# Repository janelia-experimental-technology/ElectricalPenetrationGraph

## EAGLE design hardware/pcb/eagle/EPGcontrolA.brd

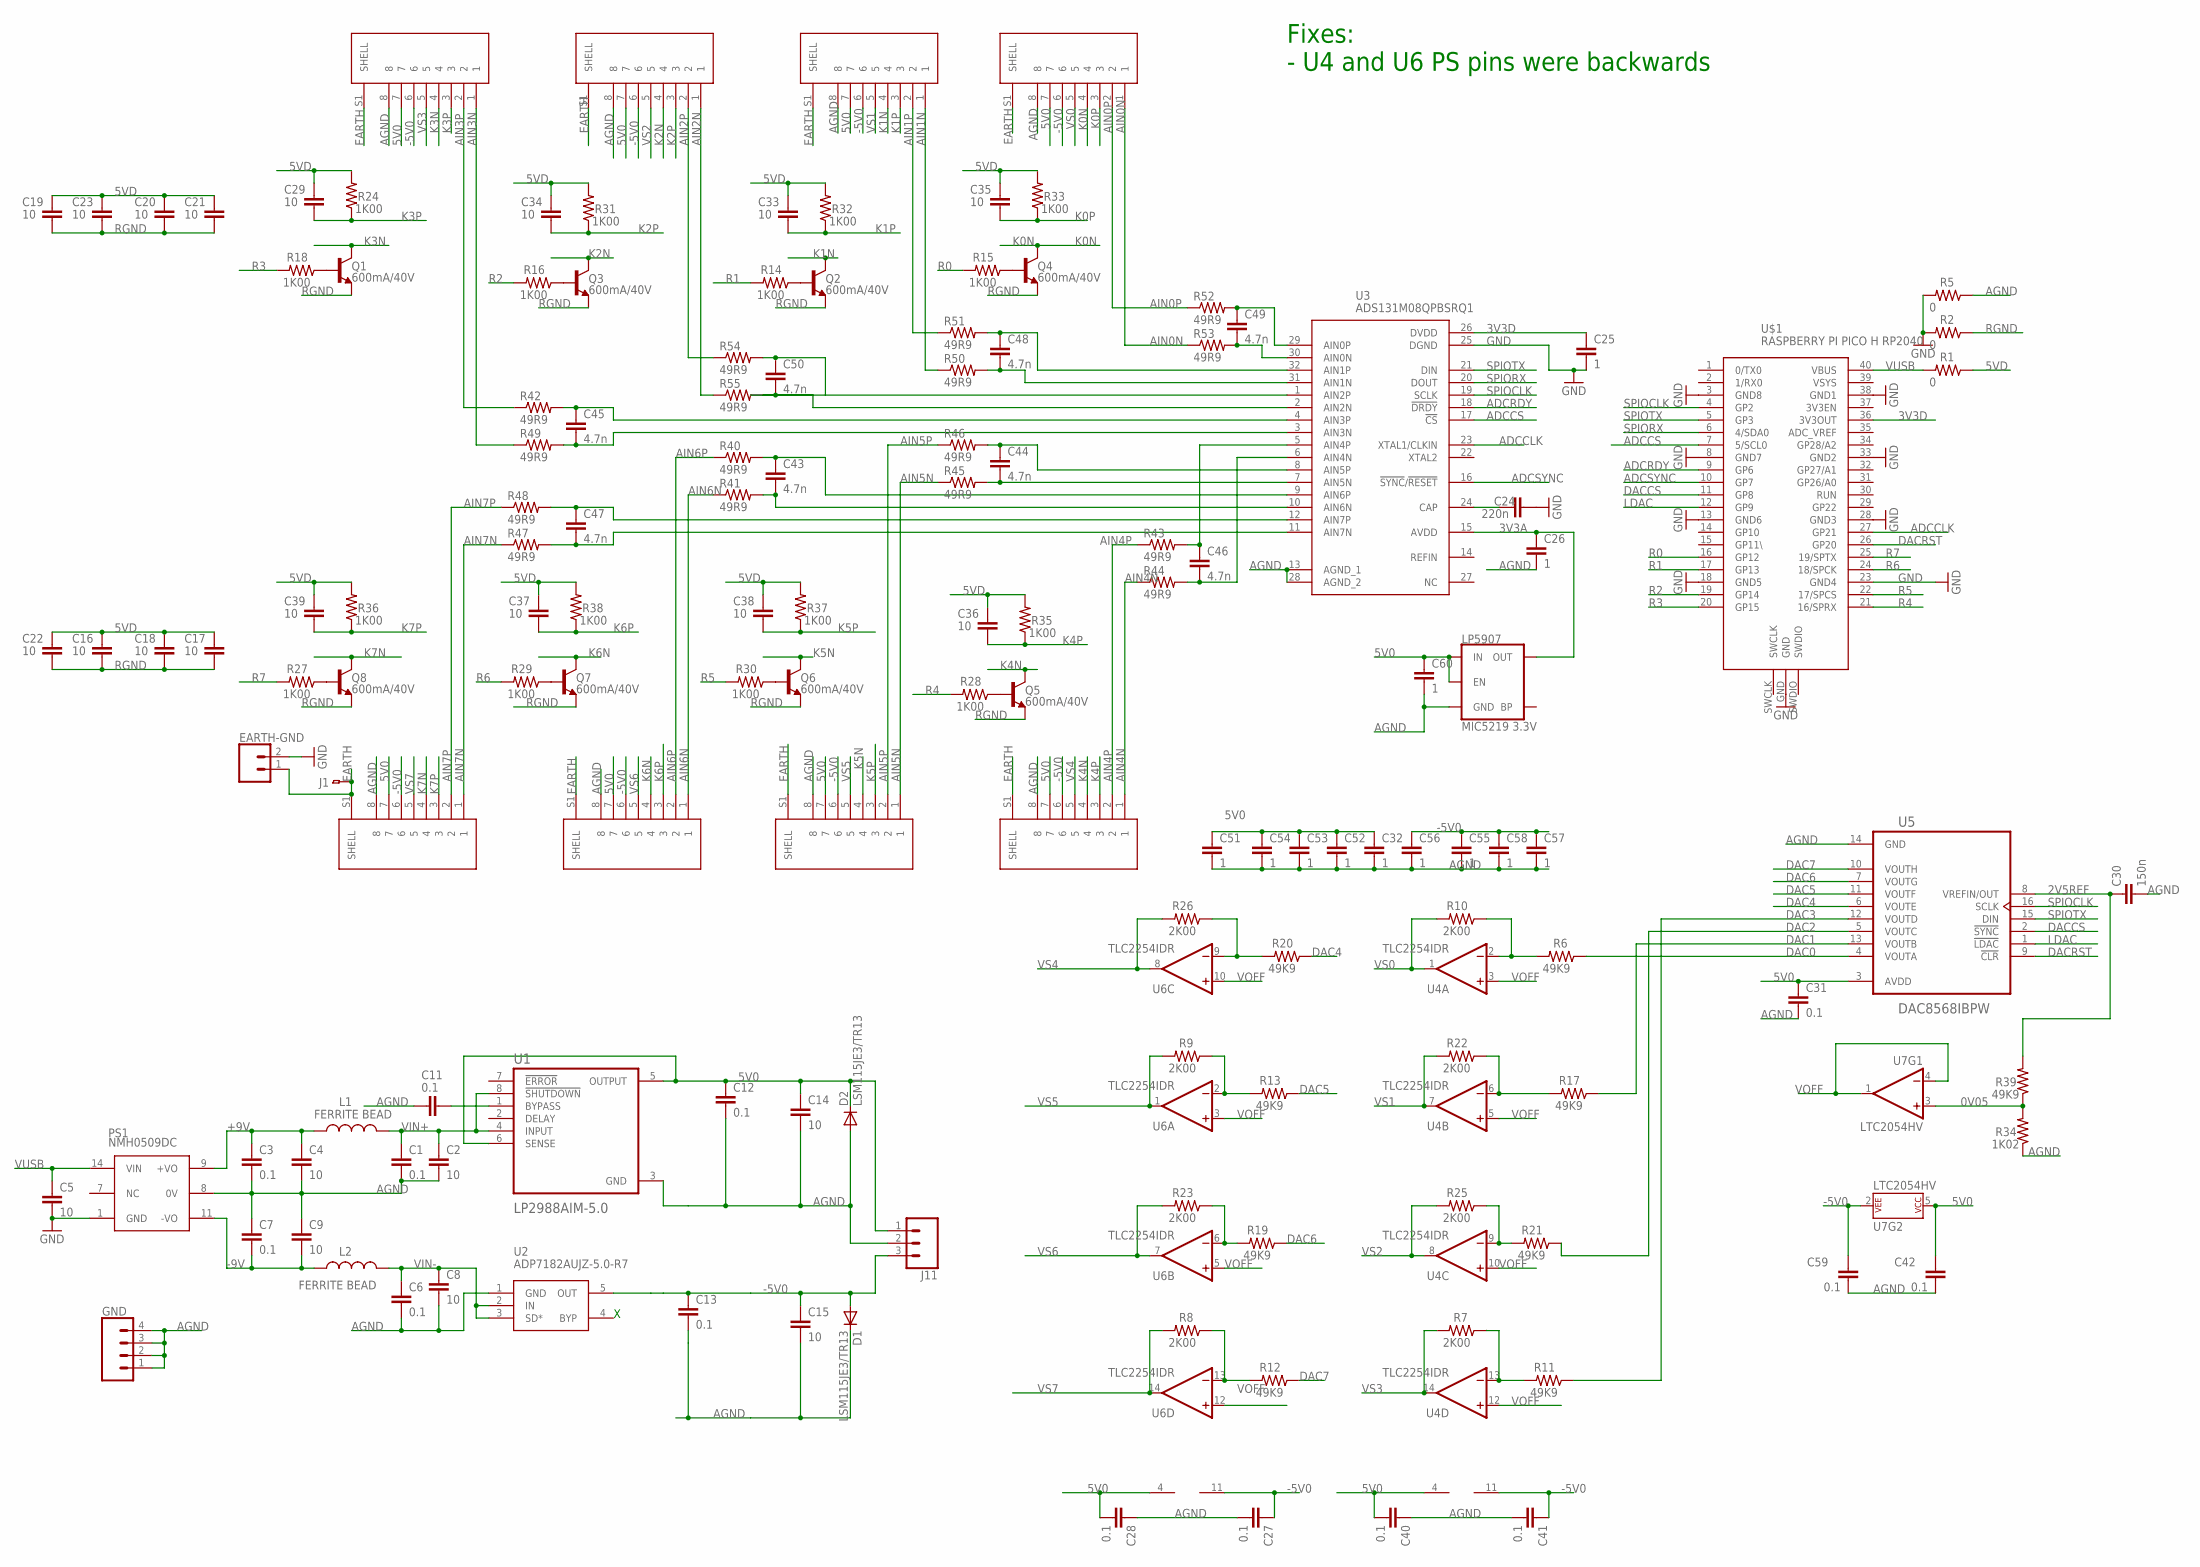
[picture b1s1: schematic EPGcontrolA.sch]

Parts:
C1, C3, C6, C7, C11, C12, C13, C27, C28, C31, C40, C41, C42, C59: 0.1; 0603S
C2, C4, C5, C8, C9, C14, C15: 10; C1206
C16, C17, C18, C19, C20, C21, C22, C23, C29, C33, C34, C35, C36, C37, C38, C39: 10; 1206S
C24: 220n; 0603S
C25, C26, C32, C51, C52, C53, C54, C55, C56, C57, C58, C60: 1; 0805S
C30: 150n; 0603S
C43, C44, C45, C46, C47, C48, C49, C50: 4.7n; 0805S
D1, D2: LSM115JE3/TR13; SMA-DIODE
EARTH-GND: CONN_02LOCK; 1X02_LOCK
GND: CONN_04LOCK; 1X04_LOCK
J1: PADPAD_040; PAD_040
J2, J3, J4, J5, J6, J7, J8, J9: 54-00248; TENSILITY_54-00248
J11: CONN_03LOCK; 1X03_LOCK
L1, L2: FERRITE BEAD; 0805S
LP5907: MIC5219 3.3V; SOT23-5
PS1: NMH0509DC; PDM2
Q1, Q2, Q3, Q4, Q5, Q6, Q7, Q8: 600mA/40V; SOT23-3
R1, R2, R5: 0; 0805S
R6, R11, R12, R13, R17, R19, R20, R21, R39: 49K9; 0805S
R7, R8, R9, R10, R22, R23, R25, R26: 2K00; 0805S
R14, R15, R16, R18, R24, R27, R28, R29, R30, R31, R32, R33, R35, R36, R37, R38: 1K00; 0805S
R34: 1K02; 0805S
R40, R41, R42, R43, R44, R45, R46, R47, R48, R49, R50, R51, R52, R53, R54, R55: 49R9; 0805S
U1: LP2988AIM-5.0; SOIC127P599X175-8N
U2: ADP7182AUJZ-5.0-R7; SOT23-5
U3: ADS131M08QPBSRQ1; QFP50P700X700X120-32N
U4, U6: TLC2254IDR; SO14
U5: DAC8568IBPW; SOP65P640X120-16N
U7: LTC2054HV; SOT23-5
U$1: RASPBERRY PI PICO H RP2040; FT_RASPBERRY-PI-PICO_TH

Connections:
0V05: R34.2, R39.1, U7.3 (+IN)
2V5REF: C30.1, R39.2, U5.8 (VREFIN/OUT)
3V3A: C26.1, LP5907.5 (OUT), U3.15 (AVDD)
3V3D: C25.1, U3.26 (DVDD), U$1.36 (3V3OUT)
5V0: C12.1, C14.1, C28.2, C31.1, C32.1, C40.2, C42.1, C51.1, C52.1, C53.1, C54.1, C60.1, D2.C, J2.7, J3.7, J4.7, J5.7, J6.7, J7.7, J8.7, J9.7, J11.1, LP5907.1 (IN), LP5907.3 (EN), U1.5 (OUTPUT), U1.6 (SENSE), U4.4 (V+), U5.3 (AVDD), U6.4 (V+), U7.5 (P$V+)
5VD: C16.1, C17.1, C18.1, C19.1, C20.1, C21.1, C22.1, C23.1, C29.1, C33.1, C34.1, C35.1, C36.1, C37.1, C38.1, C39.1, R1.1, R24.2, R31.2, R32.2, R33.2, R35.2, R36.2, R37.2, R38.2
+9V: C3.1, C4.1, L1.1, PS1.9 (+VO)
-5V0: C13.1, C15.1, C27.1, C41.1, C55.1, C56.1, C57.1, C58.1, C59.1, D1.A, J2.6, J3.6, J4.6, J5.6, J6.6, J7.6, J8.6, J9.6, J11.3, U2.5 (OUT), U4.11 (V-), U6.11 (V-), U7.2 (P$V-)
-9V: C7.2, C9.2, L2.1, PS1.11 (-VO)
A0N: C49.2, R53.2, U3.30 (AIN0N)
A0P: C49.1, R52.2, U3.29 (AIN0P)
A1N: C48.2, R50.2, U3.31 (AIN1N)
A1P: C48.1, R51.2, U3.32 (AIN1P)
A2N: C50.2, R55.2, U3.2 (AIN2N)
A2P: C50.1, R54.2, U3.1 (AIN2P)
A3N: C45.2, R49.2, U3.3 (AIN3N)
A3P: C45.1, R42.2, U3.4 (AIN3P)
A4N: C46.2, R44.2, U3.6 (AIN4N)
A4P: C46.1, R43.2, U3.5 (AIN4P)
A5N: C44.2, R45.2, U3.7 (AIN5N)
A5P: C44.1, R46.2, U3.8 (AIN5P)
A6N: C43.2, R41.2, U3.10 (AIN6N)
A6P: C43.1, R40.2, U3.9 (AIN6P)
A7N: C47.2, R47.2, U3.11 (AIN7N)
A7P: C47.1, R48.2, U3.12 (AIN7P)
ADCCLK: U3.23 (XTAL1/CLKIN), U$1.27 (GP21)
ADCCS: U3.17 (!CS), U$1.7 (5/SCL0)
ADCRDY: U3.18 (!DRDY), U$1.9 (GP6)
ADCSYNC: U3.16 (!SYNC!/!RESET), U$1.10 (GP7)
AGND: C1.2, C2.2, C3.2, C4.2, C6.2, C7.1, C8.2, C9.1, C11.2, C12.2, C13.2, C14.2, C15.2, C26.2, C27.2, C28.1, C30.2, C31.2, C32.2, C40.1, C41.2, C42.2, C51.2, C52.2, C53.2, C54.2, C55.2, C56.2, C57.2, C58.2, C59.2, C60.2, D1.C, D2.A, GND.1, GND.2, GND.3, GND.4, J2.8, J3.8, J4.8, J5.8, J6.8, J7.8, J8.8, J9.8, J11.2, LP5907.2 (GND), PS1.8 (0V), R5.1, R34.1, U1.3 (GND), U2.1 (GND), U3.13 (AGND_1), U3.28 (AGND_2), U5.14 (GND)
AIN0N: J2.1, R53.1
AIN0P: J2.2, R52.1
AIN1N: J3.1, R50.1
AIN1P: J3.2, R51.1
AIN2N: J4.1, R55.1
AIN2P: J4.2, R54.1
AIN3N: J5.1, R49.1
AIN3P: J5.2, R42.1
AIN4N: J6.1, R44.1
AIN4P: J6.2, R43.1
AIN5N: J7.1, R45.1
AIN5P: J7.2, R46.1
AIN6N: J8.1, R41.1
AIN6P: J8.2, R40.1
AIN7N: J9.1, R47.1
AIN7P: J9.2, R48.1
DAC0: R6.1, U5.4 (VOUTA)
DAC1: R17.1, U5.13 (VOUTB)
DAC2: R21.1, U5.5 (VOUTC)
DAC3: R11.1, U5.12 (VOUTD)
DAC4: R20.1, U5.6 (VOUTE)
DAC5: R13.1, U5.11 (VOUTF)
DAC6: R19.1, U5.7 (VOUTG)
DAC7: R12.1, U5.10 (VOUTH)
DACCS: U5.2 (!SYNC), U$1.11 (GP8)
DACRST: U5.9 (!CLR), U$1.26 (GP20)
EARTH: EARTH-GND.1, J1.P$1, J2.S1 (SHELL), J3.S1 (SHELL), J4.S1 (SHELL), J5.S1 (SHELL), J6.S1 (SHELL), J7.S1 (SHELL), J8.S1 (SHELL), J9.S1 (SHELL)
GND: C5.2, C24.2, C25.2, EARTH-GND.2, PS1.1 (GND), R2.2, R5.2, U3.25 (DGND), U$1.3 (GND8), U$1.8 (GND7), U$1.13 (GND6), U$1.18 (GND5), U$1.23 (GND4), U$1.28 (GND3), U$1.33 (GND2), U$1.38 (GND1), U$1.GND
K0N: J2.4, Q4.3 (C)
K0P: C35.2, J2.3, R33.1
K1N: J3.4, Q2.3 (C)
K1P: C33.2, J3.3, R32.1
K2N: J4.4, Q3.3 (C)
K2P: C34.2, J4.3, R31.1
K3N: J5.4, Q1.3 (C)
K3P: C29.2, J5.3, R24.1
K4N: J6.4, Q5.3 (C)
K4P: C36.2, J6.3, R35.1
K5N: J7.4, Q6.3 (C)
K5P: C38.2, J7.3, R37.1
K6N: J8.4, Q7.3 (C)
K6P: C37.2, J8.3, R38.1
K7N: J9.4, Q8.3 (C)
K7P: C39.2, J9.3, R36.1
LDAC: U5.1 (!LDAC), U$1.12 (GP9)
unnamed: C24.1, U3.24 (CAP)
unnamed: Q7.1 (B), R29.1
unnamed: Q8.1 (B), R27.1
unnamed: Q1.1 (B), R18.1
unnamed: Q6.1 (B), R30.1
unnamed: Q5.1 (B), R28.1
unnamed: Q4.1 (B), R15.1
unnamed: Q2.1 (B), R14.1
unnamed: C11.1, U1.1 (BYPASS)
unnamed: Q3.1 (B), R16.1
unnamed: R6.2, R10.1, U4.2 (-IN)
unnamed: R17.2, R22.1, U4.6 (-IN)
unnamed: R20.2, R26.1, U6.9 (-IN)
unnamed: R9.1, R13.2, U6.2 (-IN)
unnamed: R21.2, R25.1, U4.9 (-IN)
unnamed: R19.2, R23.1, U6.6 (-IN)
unnamed: R8.1, R12.2, U6.13 (-IN)
unnamed: R7.1, R11.2, U4.13 (-IN)
R0: R15.2, U$1.16 (GP12)
R1: R14.2, U$1.17 (GP13)
R2: R16.2, U$1.19 (GP14)
R3: R18.2, U$1.20 (GP15)
R4: R28.2, U$1.21 (16/SPRX)
R5: R30.2, U$1.22 (17/SPCS)
R6: R29.2, U$1.24 (18/SPCK)
R7: R27.2, U$1.25 (19/SPTX)
RGND: C16.2, C17.2, C18.2, C19.2, C20.2, C21.2, C22.2, C23.2, Q1.2 (E), Q2.2 (E), Q3.2 (E), Q4.2 (E), Q5.2 (E), Q6.2 (E), Q7.2 (E), Q8.2 (E), R2.1
SPIOCLK: U3.19 (SCLK), U5.16 (SCLK), U$1.4 (GP2)
SPIORX: U3.20 (DOUT), U$1.6 (4/SDA0)
SPIOTX: U3.21 (DIN), U5.15 (DIN), U$1.5 (GP3)
VIN+: C1.1, C2.1, L1.2, U1.4 (INPUT), U1.8 (!SHUTDOWN)
VIN-: C6.1, C8.1, L2.2, U2.2 (IN), U2.3 (SD*)
VOFF: U4.3 (+IN), U4.5 (+IN), U4.10 (+IN), U4.12 (+IN), U6.3 (+IN), U6.5 (+IN), U6.10 (+IN), U6.12 (+IN), U7.1 (OUT), U7.4 (-IN)
VS0: J2.5, R10.2, U4.1 (OUT)
VS1: J3.5, R22.2, U4.7 (OUT)
VS2: J4.5, R25.2, U4.8 (OUT)
VS3: J5.5, R7.2, U4.14 (OUT)
VS4: J6.5, R26.2, U6.8 (OUT)
VS5: J7.5, R9.2, U6.1 (OUT)
VS6: J8.5, R23.2, U6.7 (OUT)
VS7: J9.5, R8.2, U6.14 (OUT)
VUSB: C5.1, PS1.14 (VIN), R1.2, U$1.40 (VBUS)

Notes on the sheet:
Fixes: - U4 and U6 PS pins were backwards

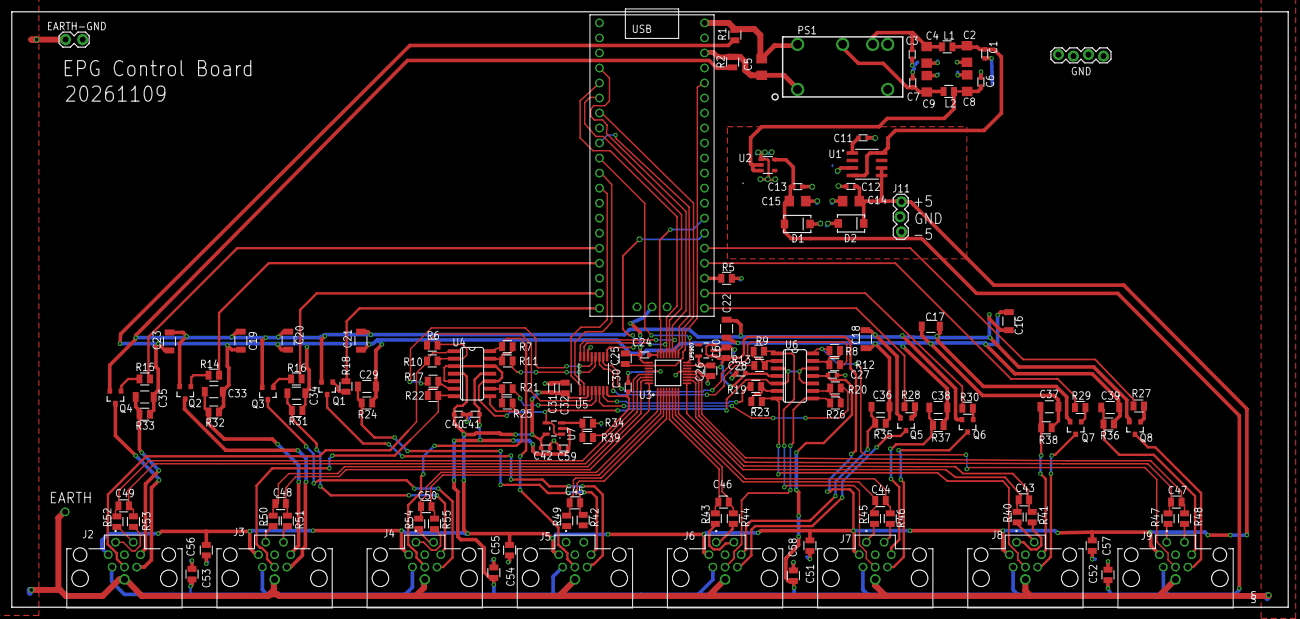
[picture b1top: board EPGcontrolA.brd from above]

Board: 2 copper layers, 215.9 x 100.7 mm, 146 parts (0 on the bottom side), 117 nets.

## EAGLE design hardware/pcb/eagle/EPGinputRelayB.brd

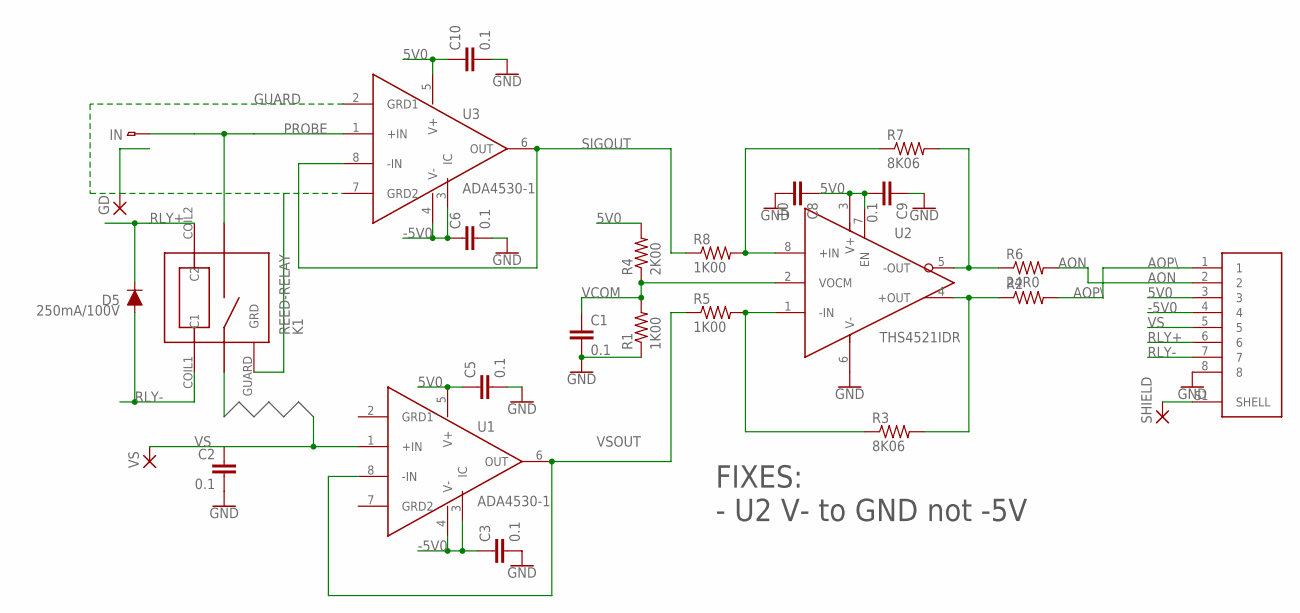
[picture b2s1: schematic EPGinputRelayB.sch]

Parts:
C1, C2, C3, C5, C6, C9, C10: 0.1; 0603S
C8: 10; 1206S
D5: 250mA/100V; SOD-323
GD: 2,15/1,0
IN: PADPAD150; PAD-150SQ
J1: 54-00251; TENSILITY_54-00248
K1: REED-RELAY; MRE05
R1, R5, R8: 1K00; 0805S
R2: RESISTOR_SM0805S; 0805S
R3, R7: 8K06; 0805S
R4: 2K00; 0805S
R6: 24R0; 0805S
SHIELD: 2,15/1,0
U1, U3: ADA4530-1; SOIC-8
U2: THS4521IDR; SOIC-8
VS: 2,15/1,0

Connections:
5V0: C5.1, C8.1, C9.2, C10.1, J1.3, R4.2, U1.5 (V+), U2.3 (V+), U2.7 (EN), U3.5 (V+)
-5V0: C3.1, C6.1, J1.4, U1.3 (IC), U1.4 (V-), U3.3 (IC), U3.4 (V-)
AON: J1.2, R6.2
AOP\: J1.1, R2.2
GND: C1.2, C2.2, C3.2, C5.2, C6.2, C8.2, C9.1, C10.2, J1.8, R1.1, U2.6 (V-)
GUARD: GD.1, K1.GUARD (GRD), U3.2 (GRD1), U3.7 (GRD2)
unnamed: J1.S1 (SHELL), SHIELD.1
unnamed: R7.1, R8.2, U2.8 (+IN)
unnamed: R3.1, R5.2, U2.1 (-IN)
unnamed: R2.1, R3.2, U2.4 (+OUT)
unnamed: R6.1, R7.2, U2.5 (-OUT)
PROBE: IN.P$1, U3.1 (+IN)
RLY+: D5.C, J1.6, K1.COIL2 (C2)
RLY-: D5.A, J1.7, K1.COIL1 (C1)
SIGOUT: R8.1, U3.6 (OUT), U3.8 (-IN)
VCOM: C1.1, R1.2, R4.1, U2.2 (VOCM)
VS: C2.1, J1.5, U1.1 (+IN), VS.1
VSOUT: R5.1, U1.6 (OUT), U1.8 (-IN)

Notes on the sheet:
FIXES: - U2 V- to GND not -5V

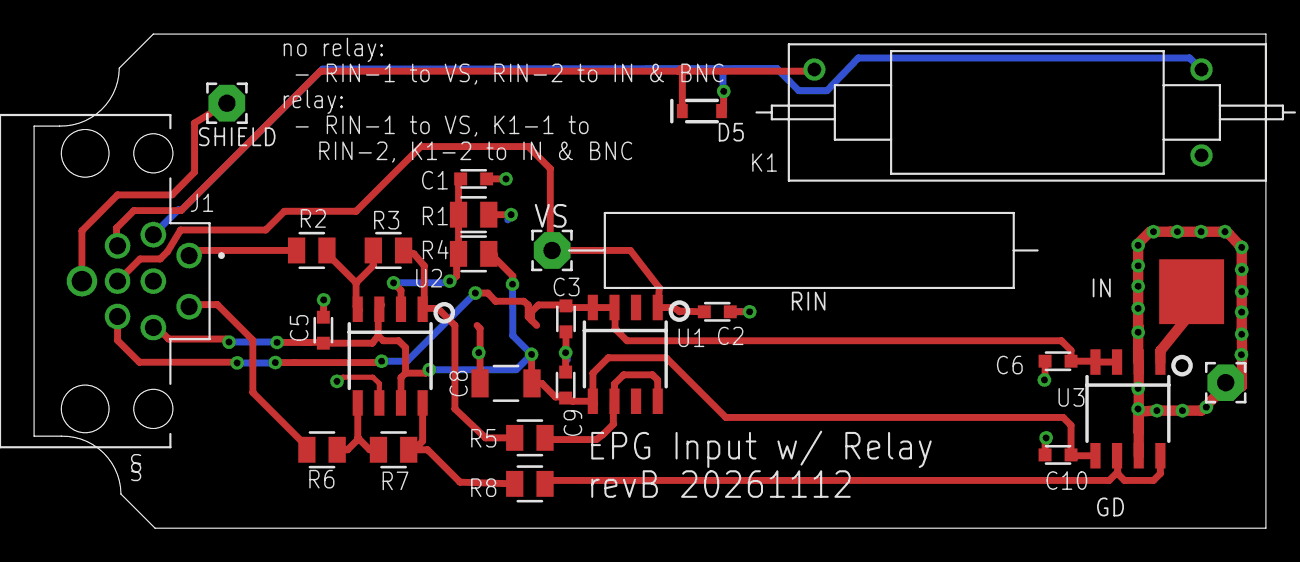
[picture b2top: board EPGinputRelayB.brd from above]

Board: 2 copper layers, 72.3 x 29.0 mm, 28 parts (0 on the bottom side), 18 nets.

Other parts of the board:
RIN: 1GRES
U$1: BNC

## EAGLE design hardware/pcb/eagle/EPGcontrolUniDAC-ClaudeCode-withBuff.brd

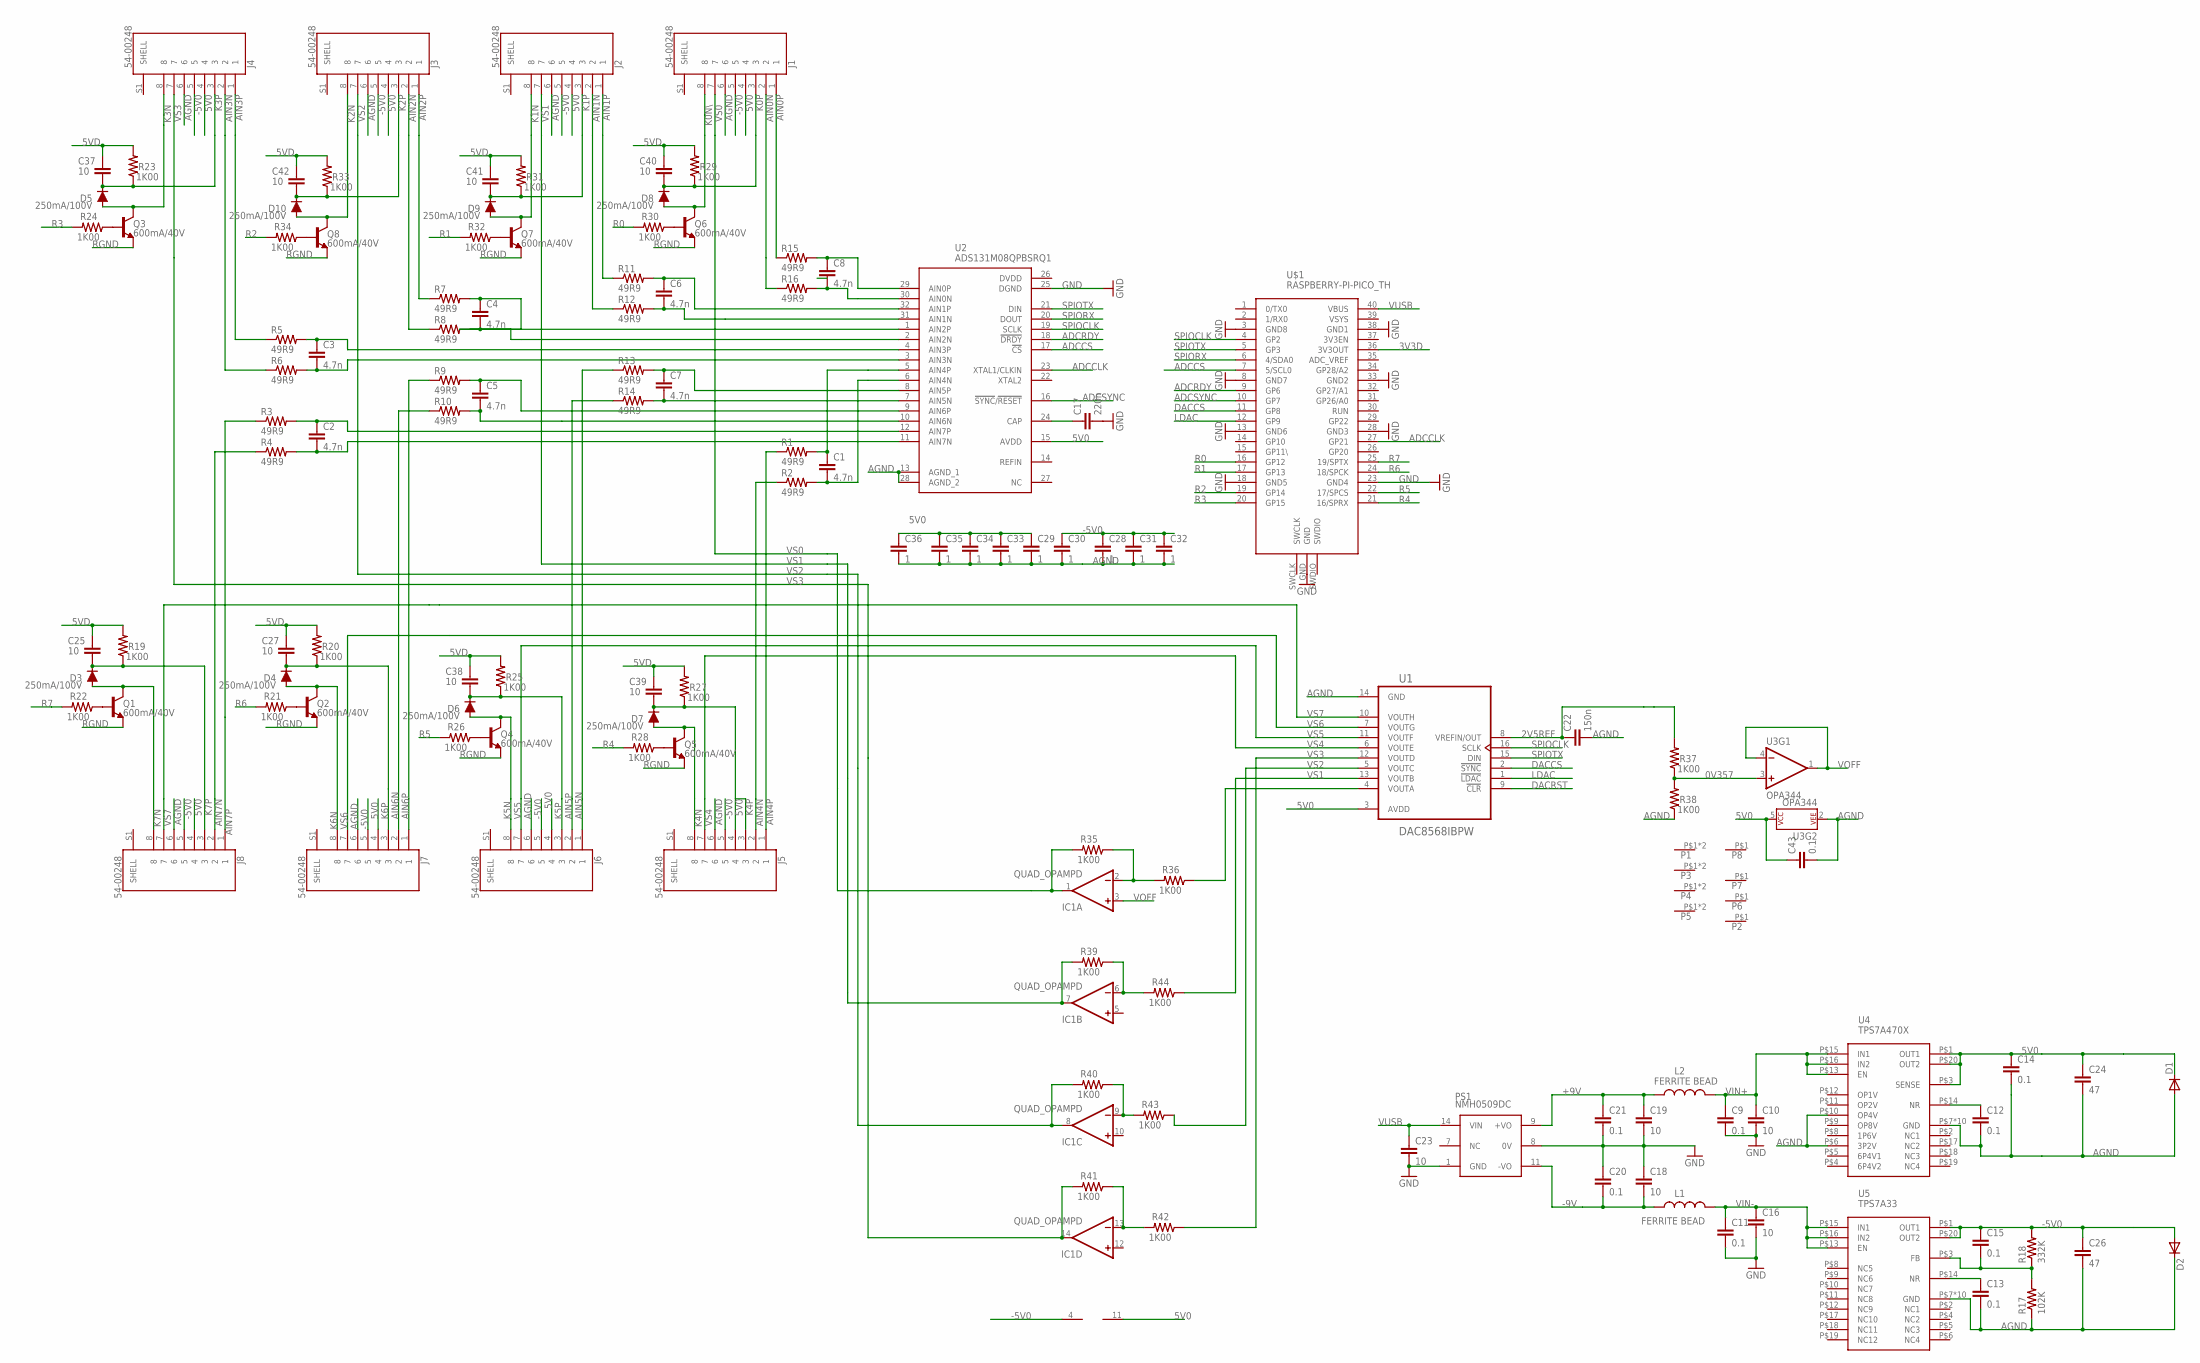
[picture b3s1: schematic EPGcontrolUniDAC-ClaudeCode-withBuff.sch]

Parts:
C1, C2, C3, C4, C5, C6, C7, C8: 4.7n; 0603S
C9, C11, C12, C13, C14, C15, C20, C21, C43: 0.1; 0603S
C10, C16, C18, C19, C23: 10; C1206
C17: 220n; 0603S
C22: 150n; 0603S
C24, C26: 47; C1206
C25, C27, C37, C38, C39, C40, C41, C42: 10; 1206S
C28, C29, C30, C31, C32, C33, C34, C35, C36: 1; 0805S
D1, D2: DIODESMA; SMA-DIODE
D3, D4, D5, D6, D7, D8, D9, D10: 250mA/100V; SOD-323
IC1: QUAD_OPAMPD; SO14
J1, J2, J3, J4, J5, J6, J7, J8: 54-00248; TENSILITY_54-00248
L1, L2: FERRITE BEAD; 0805S
P1, P3, P4, P5: CON1BANANA; BANANA_105-0754-001
P2, P6, P7, P8: CON1574; 574
PS1: NMH0509DC; PDM2
Q1, Q2, Q3, Q4, Q5, Q6, Q7, Q8: 600mA/40V; SOT23-3
R1, R2, R3, R4, R5, R6, R7, R8, R9, R10, R11, R12, R13, R14, R15, R16: 49R9; 0805S
R17: 102K; R0805
R18: 332K; R0805
R19, R20, R21, R22, R23, R24, R25, R26, R27, R28, R29, R30, R31, R32, R33, R34, R35, R36, R37, R38, R39, R40, R41, R42, R43, R44: 1K00; 0805S
U1: DAC8568IBPW; SOP65P640X120-16N
U2: ADS131M08QPBSRQ1; QFP50P700X700X120-32N
U3: OPA344; SOT23-5
U4: TPS7A470X; VQFN-20-5X5
U5: TPS7A33; VQFN-20-5X5
U$1: RASPBERRY-PI-PICO_TH; FT_RASPBERRY-PI-PICO_TH

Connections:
0V357: R37.1, R38.2, U3.3 (+IN)
2V5REF: C22.1, R37.2, U1.8 (VREFIN/OUT)
3V3D: U$1.36 (3V3OUT)
5V0: C14.1, C24.1, C29.1, C33.1, C34.1, C35.1, C36.1, C43.1, D1.C, IC1.11 (V-), J1.4, J2.4, J3.4, J4.4, J5.4, J6.4, J7.4, J8.4, U1.3 (AVDD), U2.15 (AVDD), U3.5 (P$V+), U4.P$1 (OUT1), U4.P$3 (SENSE), U4.P$20 (OUT2)
5VD: C25.1, C27.1, C37.1, C38.1, C39.1, C40.1, C41.1, C42.1, R19.2, R20.2, R23.2, R25.2, R27.2, R29.2, R31.2, R33.2
+9V: C19.1, C21.1, L2.1, PS1.9 (+VO)
-5V0: C15.1, C26.1, C28.1, C30.1, C31.1, C32.1, D2.A, IC1.4 (V+), J1.5, J2.5, J3.5, J4.5, J5.5, J6.5, J7.5, J8.5, R18.2, U5.P$1 (OUT1), U5.P$20 (OUT2)
-9V: C18.2, C20.2, L1.1, PS1.11 (-VO)
A0N: C8.2, R16.2, U2.30 (AIN0N)
A0P: C8.1, R15.2, U2.29 (AIN0P)
A1N: C6.2, R12.2, U2.31 (AIN1N)
A1P: C6.1, R11.2, U2.32 (AIN1P)
A2N: C4.2, R8.2, U2.2 (AIN2N)
A2P: C4.1, R7.2, U2.1 (AIN2P)
A3N: C3.2, R6.2, U2.3 (AIN3N)
A3P: C3.1, R5.2, U2.4 (AIN3P)
A4N: C1.2, R2.2, U2.6 (AIN4N)
A4P: C1.1, R1.2, U2.5 (AIN4P)
A5N: C7.2, R14.2, U2.7 (AIN5N)
A5P: C7.1, R13.2, U2.8 (AIN5P)
A6N: C5.2, R10.2, U2.10 (AIN6N)
A6P: C5.1, R9.2, U2.9 (AIN6P)
A7N: C2.2, R4.2, U2.11 (AIN7N)
A7P: C2.1, R3.2, U2.12 (AIN7P)
ADCCLK: U2.23 (XTAL1/CLKIN), U$1.27 (GP21)
ADCCS: U2.17 (!CS), U$1.7 (5/SCL0)
ADCRDY: U2.18 (!DRDY), U$1.9 (GP6)
ADCSYNC: U2.16 (!SYNC!/!RESET), U$1.10 (GP7)
AGND: C12.2, C13.2, C14.2, C22.2, C24.2, C26.2, C28.2, C29.2, C30.2, C31.2, C32.2, C33.2, C34.2, C35.2, C36.2, C43.2, D1.A, D2.C, J1.6, J2.6, J3.6, J4.6, J5.6, J6.6, J7.6, J8.6, R17.1, R38.1, U1.14 (GND), U2.13 (AGND_1), U2.28 (AGND_2), U3.2 (P$V-), U4.P$6 (3P2V), U4.P$7 (GND), U4.P$10 (OP4V), U4.PAD1 (GND), U4.PAD2 (GND), U4.PAD3 (GND), U4.PAD4 (GND), U4.PAD5 (GND), U4.PAD6 (GND), U4.PAD7 (GND), U4.PAD8 (GND), U4.PAD9 (GND), U5.P$7 (GND), U5.PAD1 (GND), U5.PAD2 (GND), U5.PAD3 (GND), U5.PAD4 (GND), U5.PAD5 (GND), U5.PAD6 (GND), U5.PAD7 (GND), U5.PAD8 (GND), U5.PAD9 (GND)
AIN0N: J1.2, R16.1
AIN0P: J1.1, R15.1
AIN1N: J2.2, R12.1
AIN1P: J2.1, R11.1
AIN2N: J3.2, R8.1
AIN2P: J3.1, R7.1
AIN3N: J4.2, R6.1
AIN3P: J4.1, R5.1
AIN4N: J5.2, R2.1
AIN4P: J5.1, R1.1
AIN5N: J6.1, R13.1
AIN5P: J6.2, R14.1
AIN6N: J7.2, R10.1
AIN6P: J7.1, R9.1
AIN7N: J8.2, R4.1
AIN7P: J8.1, R3.1
DACCS: U1.2 (!SYNC), U$1.11 (GP8)
DACRST: U1.9 (!CLR)
GND: C9.2, C10.2, C11.2, C16.2, C17.2, C18.1, C19.2, C20.1, C21.2, C23.2, PS1.1 (GND), PS1.8 (0V), U2.25 (DGND), U$1.3 (GND8), U$1.8 (GND7), U$1.13 (GND6), U$1.18 (GND5), U$1.23 (GND4), U$1.28 (GND3), U$1.33 (GND2), U$1.38 (GND1), U$1.GND
K0N\: D8.A, J1.8, Q6.3 (C)
K0P: C40.2, D8.C, J1.3, R29.1
K1N: D9.A, J2.8, Q7.3 (C)
K1P: C41.2, D9.C, J2.3, R31.1
K2N: D10.A, J3.8, Q8.3 (C)
K2P: C42.2, D10.C, J3.3, R33.1
K3N: D5.A, J4.8, Q3.3 (C)
K3P: C37.2, D5.C, J4.3, R23.1
K4N: D7.A, J5.8, Q5.3 (C)
K4P: C39.2, D7.C, J5.3, R27.1
K5N: D6.A, J6.8, Q4.3 (C)
K5P: C38.2, D6.C, J6.3, R25.1
K6N: D4.A, J7.8, Q2.3 (C)
K6P: C27.2, D4.C, J7.3, R20.1
K7N: D3.A, J8.8, Q1.3 (C)
K7P: C25.2, D3.C, J8.3, R19.1
LDAC: U1.1 (!LDAC), U$1.12 (GP9)
unnamed: C15.2, R17.2, R18.1, U5.P$3 (FB)
unnamed: C17.1, U2.24 (CAP)
unnamed: Q2.1 (B), R21.1
unnamed: Q1.1 (B), R22.1
unnamed: Q3.1 (B), R24.1
unnamed: Q4.1 (B), R26.1
unnamed: Q5.1 (B), R28.1
unnamed: Q6.1 (B), R30.1
unnamed: Q7.1 (B), R32.1
unnamed: R36.1, U1.4 (VOUTA)
unnamed: Q8.1 (B), R34.1
unnamed: IC1.2 (-IN), R35.1, R36.2
unnamed: IC1.6 (-IN), R39.1, R44.2
unnamed: R44.1, U1.13 (VOUTB)
unnamed: C13.1, U5.P$14 (NR)
unnamed: R43.1, U1.5 (VOUTC)
unnamed: IC1.9 (-IN), R40.1, R43.2
unnamed: C12.1, U4.P$14 (NR)
unnamed: IC1.13 (-IN), R41.1, R42.2
unnamed: R42.1, U1.12 (VOUTD)
R0: R30.2, U$1.16 (GP12)
R1: R32.2, U$1.17 (GP13)
R2: R34.2, U$1.19 (GP14)
R3: R24.2, U$1.20 (GP15)
R4: R28.2, U$1.21 (16/SPRX)
R5: R26.2, U$1.22 (17/SPCS)
R6: R21.2, U$1.24 (18/SPCK)
R7: R22.2, U$1.25 (19/SPTX)
RGND: Q1.2 (E), Q2.2 (E), Q3.2 (E), Q4.2 (E), Q5.2 (E), Q6.2 (E), Q7.2 (E), Q8.2 (E)
SPIOCLK: U1.16 (SCLK), U2.19 (SCLK), U$1.4 (GP2)
SPIORX: U2.20 (DOUT), U$1.6 (4/SDA0)
SPIOTX: U1.15 (DIN), U2.21 (DIN), U$1.5 (GP3)
VIN+: C9.1, C10.1, L2.2, U4.P$13 (EN), U4.P$15 (IN1), U4.P$16 (IN2)
VIN-: C11.1, C16.1, L1.2, U5.P$13 (EN), U5.P$15 (IN1), U5.P$16 (IN2)
VOFF: IC1.3 (+IN), U3.1 (OUT), U3.4 (-IN)
VS0: IC1.1 (OUT), J1.7, R35.2
VS1: IC1.7 (OUT), J2.7, R39.2
VS2: IC1.8 (OUT), J3.7, R40.2
VS3: IC1.14 (OUT), J4.7, R41.2
VS4: J5.7, U1.6 (VOUTE)
VS5: J6.7, U1.11 (VOUTF)
VS6: J7.7, U1.7 (VOUTG)
VS7: J8.7, U1.10 (VOUTH)
VUSB: C23.1, PS1.14 (VIN), U$1.40 (VBUS)

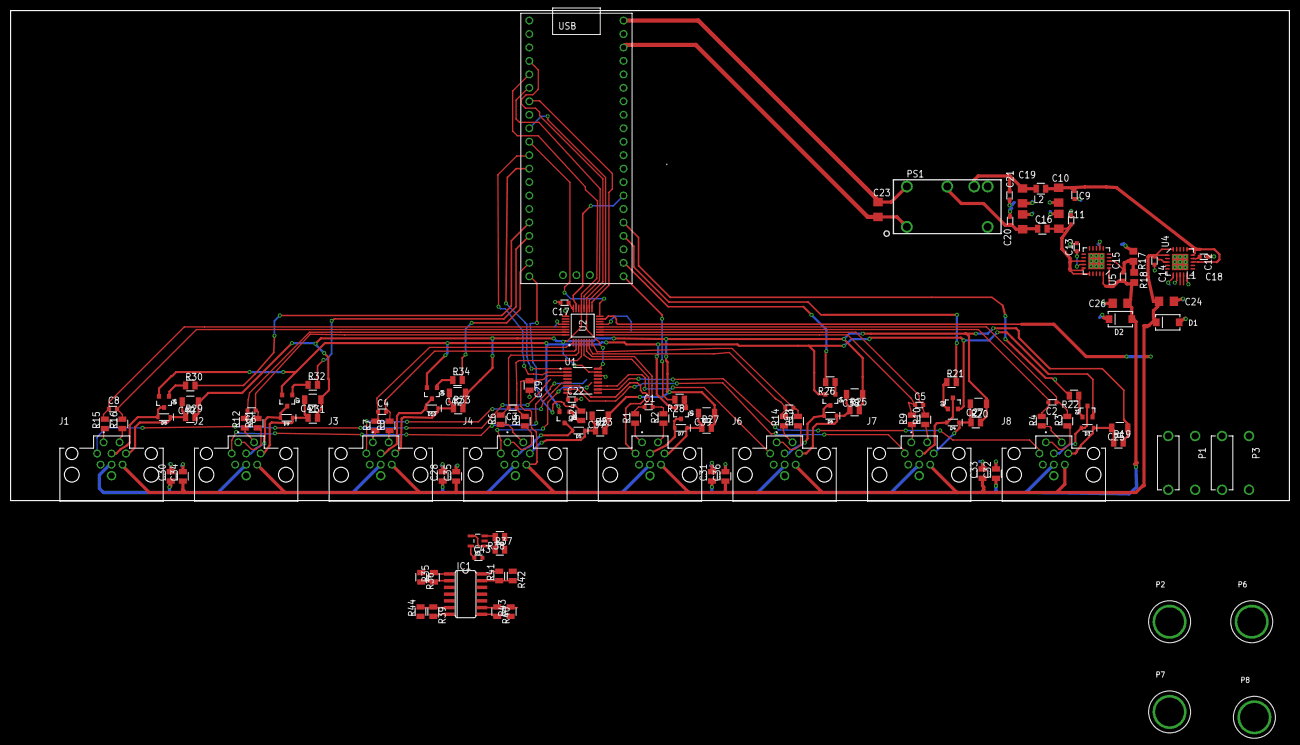
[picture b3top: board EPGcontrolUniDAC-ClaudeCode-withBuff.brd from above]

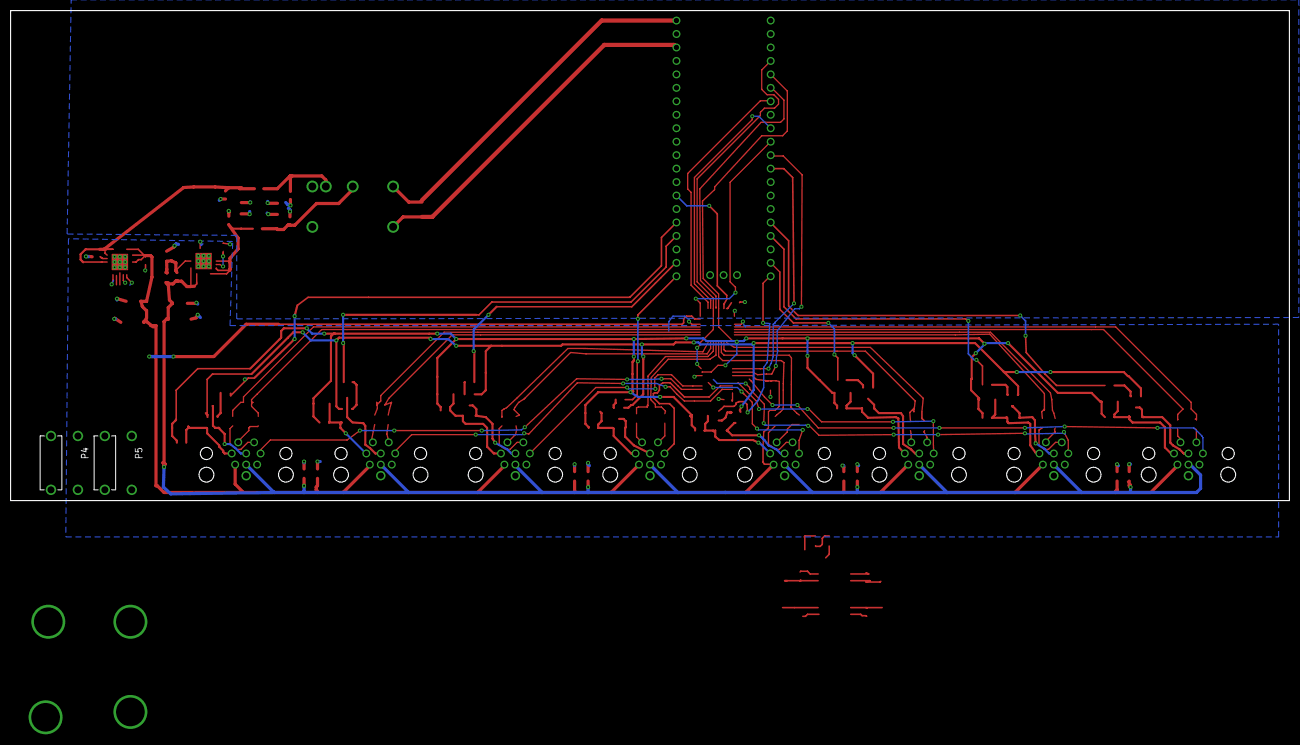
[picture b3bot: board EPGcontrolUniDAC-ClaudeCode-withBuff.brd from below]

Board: 2 copper layers, 241.3 x 92.5 mm, 131 parts (2 on the bottom side), 107 nets.

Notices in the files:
parts and their libraries:
SparkFun-DiscreteSemi: Licensing: Creative Commons ShareAlike 4.0 International - https://creativecommons.org/licenses/by-sa/4.0
